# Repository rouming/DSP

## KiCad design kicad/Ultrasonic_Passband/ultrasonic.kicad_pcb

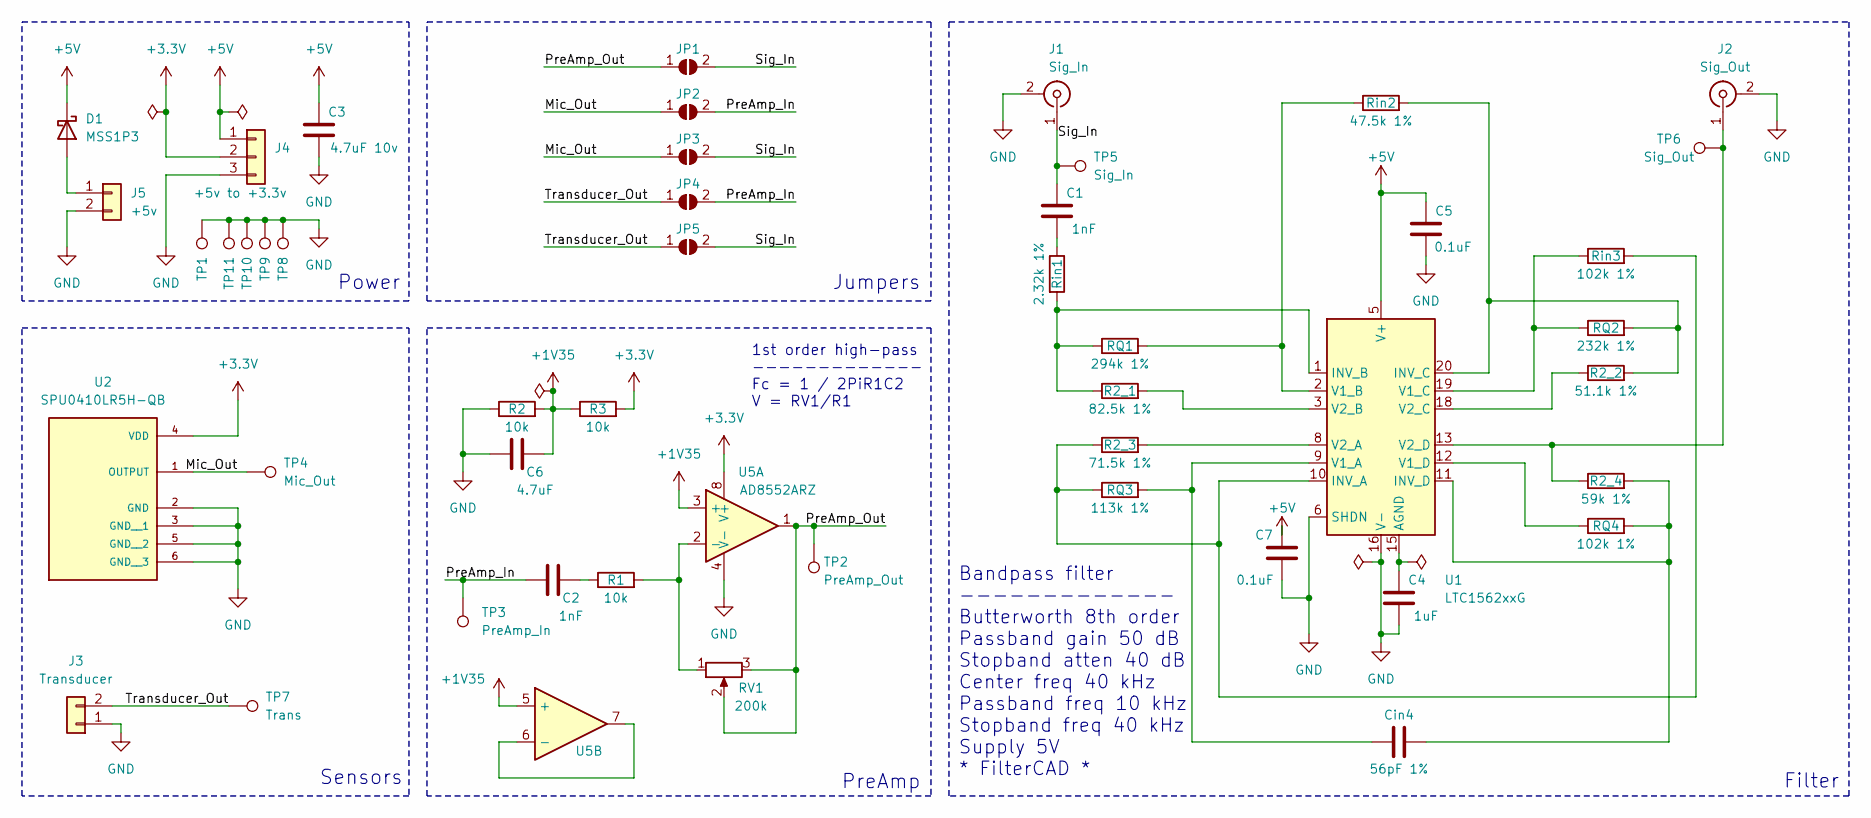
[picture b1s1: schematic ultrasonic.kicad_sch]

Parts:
C1, C2: 1nF; C_0603_1608Metric
C3: 4.7uF 10v; C_0603_1608Metric
C4: 1uF; C_0603_1608Metric
C5, C7: 0.1uF; C_0603_1608Metric
C6: 4.7uF; C_0603_1608Metric
Cin4: 56pF 1%; C_0603_1608Metric
D1: MSS1P3; D_MicroSMP_AK
J1: Sig_In; U.FL_Molex_MCRF_73412-0110_Vertical
J2: Sig_Out; U.FL_Molex_MCRF_73412-0110_Vertical
J3: Transducer; JST_XH_B2B-XH-A_1x02_P2.50mm_Vertical
J4: +5v to +3.3v; PinHeader_1x03_P2.54mm_Vertical
J5: +5v; PinHeader_1x02_P2.54mm_Vertical
JP1: PreAmp > Sig; SolderJumper-2_P1.3mm_Open_RoundedPad1.0x1.5mm
JP2: Mic > PreAmp; SolderJumper-2_P1.3mm_Open_RoundedPad1.0x1.5mm
JP3: Mic > Sig; SolderJumper-2_P1.3mm_Open_RoundedPad1.0x1.5mm
JP4: Trans > PreAmp; SolderJumper-2_P1.3mm_Open_RoundedPad1.0x1.5mm
JP5: Trans > Sig; SolderJumper-2_P1.3mm_Open_RoundedPad1.0x1.5mm
R1, R2, R3: 10k; R_0603_1608Metric
R2_1: 82.5k 1%; R_0603_1608Metric
R2_2: 51.1k 1%; R_0603_1608Metric
R2_3: 71.5k 1%; R_0603_1608Metric
R2_4: 59k 1%; R_0603_1608Metric
RQ1: 294k 1%; R_0603_1608Metric
RQ2: 232k 1%; R_0603_1608Metric
RQ3: 113k 1%; R_0603_1608Metric
RQ4: 102k 1%; R_0603_1608Metric
RV1: 200k; Potentiometer_Bourns_3296W_Vertical
Rin1: 2.32k 1%; R_0603_1608Metric
Rin2: 47.5k 1%; R_0603_1608Metric
Rin3: 102k 1%; R_0603_1608Metric
TP1, TP8, TP9, TP10, TP11: GND; TestPoint_Pad_D2.0mm
TP2: PreAmp_Out; TestPoint_Pad_D2.0mm
TP3: PreAmp_In; TestPoint_Pad_D2.0mm
TP4: Mic_Out; TestPoint_Pad_D2.0mm
TP5: Sig_In; TestPoint_Pad_D2.0mm
TP6: Sig_Out; TestPoint_Pad_D2.0mm
TP7: Trans; TestPoint_Pad_D2.0mm
U1: LTC1562xxG; SSOP-20_5.3x7.2mm_P0.65mm
U2: SPU0410LR5H-QB; XDCR_SPU0410LR5H-QB_aisler; PARTREV H
U5: AD8552ARZ; SOIC-8_3.9x4.9mm_P1.27mm

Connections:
+1V35: C6.1, R2.2, R3.1, U5.3 (+), U5.5 (+)
+3.3V: J4.2, R3.2, U2.4 (VDD), U5.8 (V+)
+5V: C3.1, C5.2, C7.2, D1.1 (K), J4.1, U1.5 (V+)
/Mic_Out: JP2.1 (A), JP3.1 (A), TP4.1, U2.1 (OUTPUT)
/PreAmp_In: C2.2, JP2.2 (B), JP4.2 (B), TP3.1
/PreAmp_Out: JP1.1 (A), RV1.2, RV1.3, TP2.1, U5.1
/Sig_In: C1.2, J1.1 (In), JP1.2 (B), JP3.2 (B), JP5.2 (B), TP5.1
/Transducer_Out: J3.2, JP4.1 (A), JP5.1 (A), TP7.1
GND: C3.2, C4.1, C5.1, C6.2, C7.1, J1.2 (Ext), J2.2 (Ext), J3.1, J4.3, J5.2, R2.1, TP1.1, TP8.1, TP9.1, TP10.1, TP11.1, U1.4 (V-), U1.6 (SHDN), U1.7 (V-), U1.14 (V-), U1.16 (V-), U1.17 (V-), U2.2 (GND), U2.3 (GND__1), U2.5 (GND__2), U2.6 (GND__3), U5.4 (V-)
unnamed: C1.1, Rin1.1
unnamed: C2.1, R1.1
unnamed: D1.2 (A), J5.1
unnamed: J2.1 (In), R2_4.1, TP6.1, U1.13 (V2_D)
unnamed: C4.2, U1.15 (AGND)
unnamed: R2_3.1, RQ3.1, Rin3.2, U1.10 (INV_A)
unnamed: R2_1.1, RQ1.1, Rin1.2, U1.1 (INV_B)
unnamed: R2_2.2, RQ2.2, Rin2.2, U1.20 (INV_C)
unnamed: Cin4.2, R2_4.2, RQ4.2, U1.11 (INV_D)
unnamed: Cin4.1, RQ3.2, U1.9 (V1_A)
unnamed: RQ1.2, Rin2.1, U1.2 (V1_B)
unnamed: RQ2.1, Rin3.1, U1.19 (V1_C)
unnamed: RQ4.1, U1.12 (V1_D)
unnamed: R2_3.2, U1.8 (V2_A)
unnamed: R2_1.2, U1.3 (V2_B)
unnamed: R2_2.1, U1.18 (V2_C)
unnamed: R1.2, RV1.1, U5.2 (-)
unnamed: U5.6 (-), U5.7

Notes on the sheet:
Jumpers
Bandpass filter ------------- Butterworth 8th order Passband gain 50 dB Stopband atten 40 dB Center freq 40 kHz Passband freq 10 kHz Stopband freq 40 kHz Supply 5V * FilterCAD *
Filter
Power
1st order high-pass ------------- Fc = 1 / 2PiR1C2 V = RV1/R1
PreAmp
Sensors

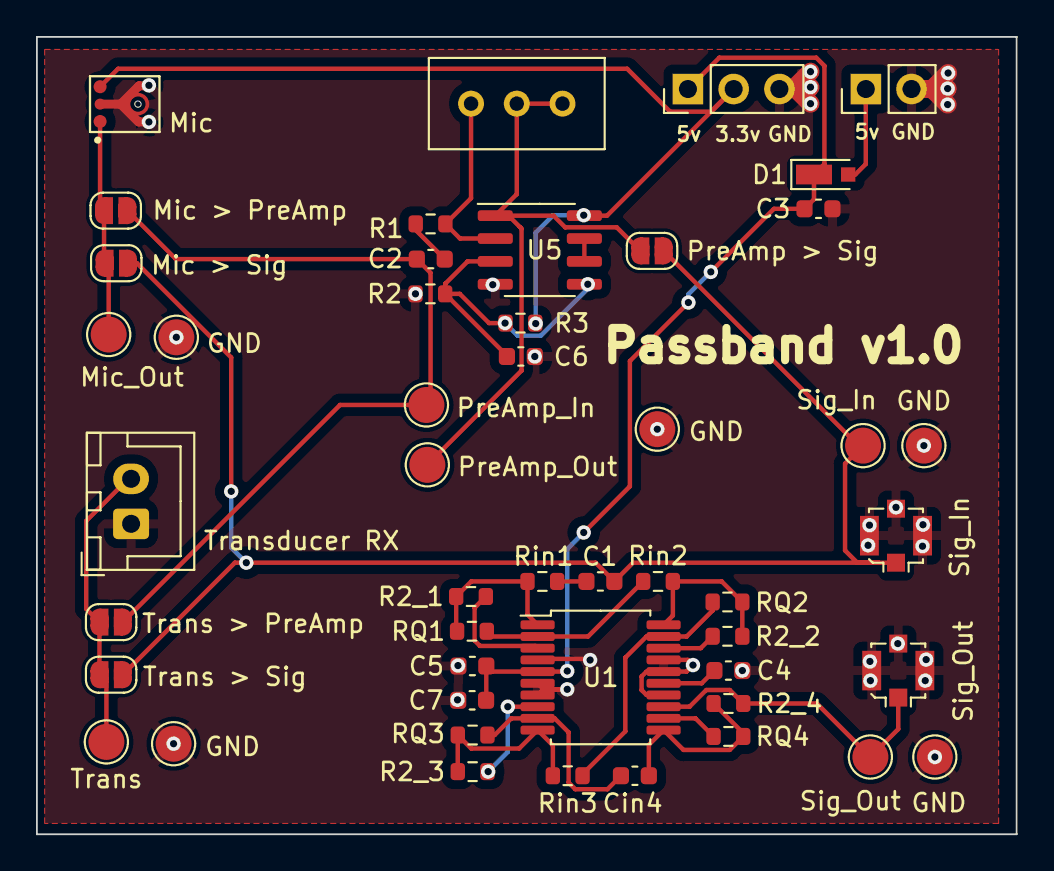
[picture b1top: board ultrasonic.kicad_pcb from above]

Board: 2 copper layers, 54.4 x 44.3 mm, 48 parts (0 on the bottom side), 27 nets.

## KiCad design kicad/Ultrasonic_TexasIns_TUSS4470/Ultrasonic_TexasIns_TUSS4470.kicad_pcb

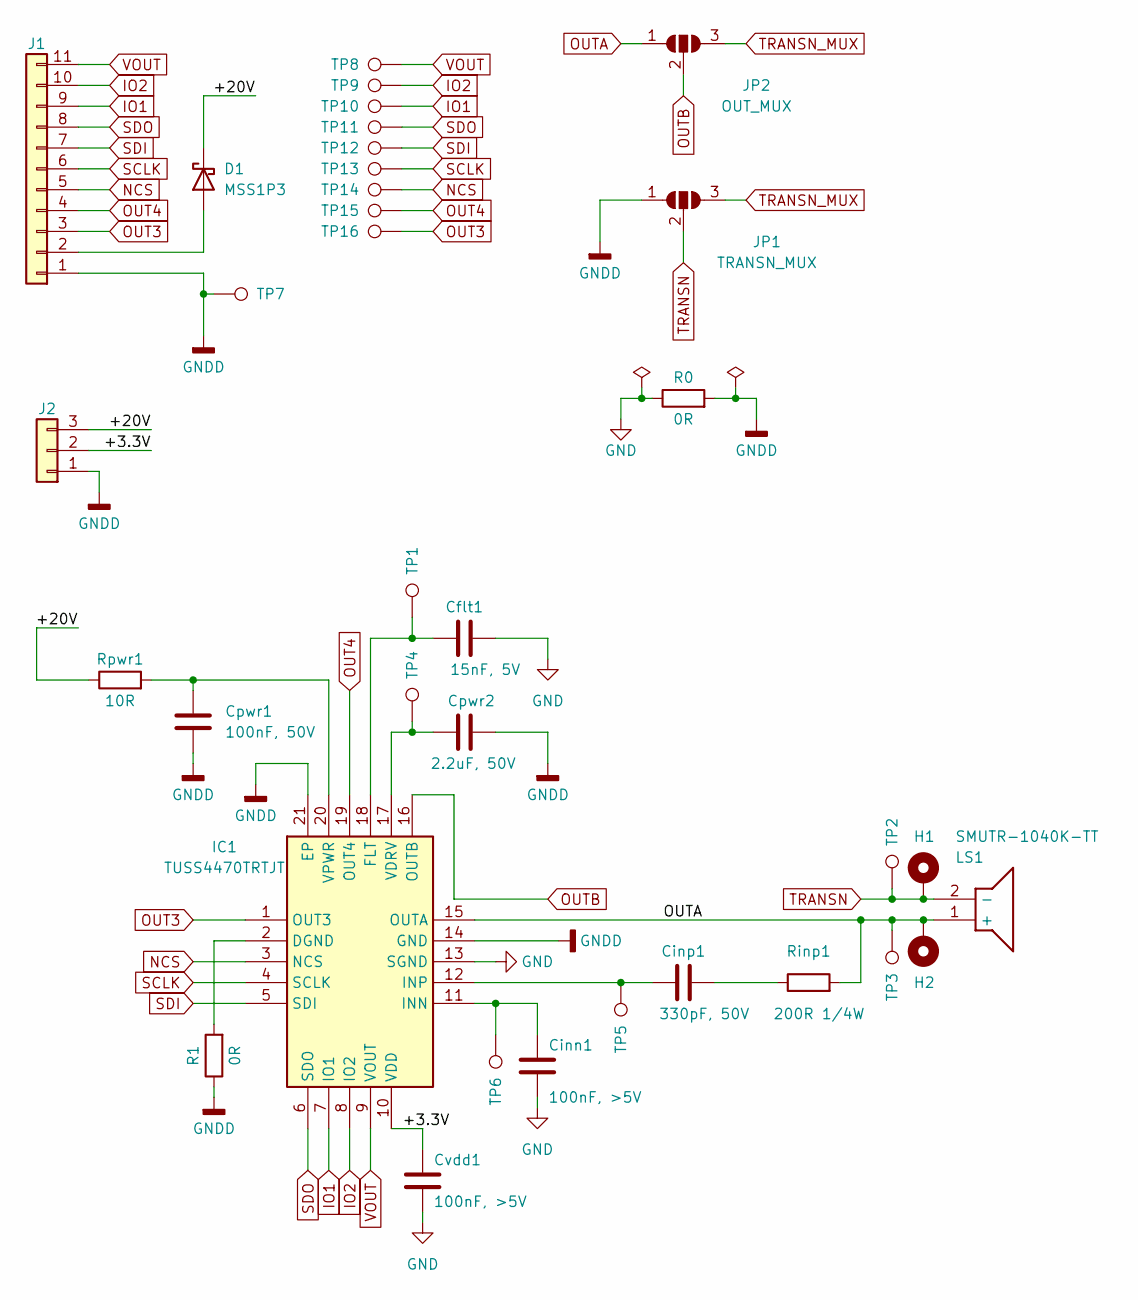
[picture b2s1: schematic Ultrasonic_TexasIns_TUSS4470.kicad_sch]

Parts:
Cflt1: 15nF, 5V; C_0603_1608Metric
Cinn1: 100nF, >5V; C_0603_1608Metric
Cinp1: 330pF, 50V; C_0603_1608Metric
Cpwr1: 100nF, 50V; C_0603_1608Metric
Cpwr2: 2.2uF, 50V; C_0805_2012Metric
Cvdd1: 100nF, >5V; C_0603_1608Metric
D1: MSS1P3; D_MicroSMP_AK
H1, H2: MountingHole_Pad; MountingHole_2.2mm_M2_DIN965_Pad
IC1: TUSS4470TRTJT; QFN50P400X400X80-21N-D; Manufacturer_Part_Number TUSS4470TRTJT; Mouser Part Number 595-TUSS4470TRTJT
J1: PinHeader_1x11_P2.54mm_Vertical
J2: PinHeader_1x03_P2.54mm_Vertical
JP1: TRANSN_MUX; SolderJumper-3_P1.3mm_Open_Pad1.0x1.5mm
JP2: OUT_MUX; SolderJumper-3_P1.3mm_Open_Pad1.0x1.5mm
LS1: SMUTR-1040K-TT; SMUTR1040KTT; Manufacturer_Part_Number SMUTR-1040K-TT
R0, R1: 0R; R_0603_1608Metric
Rinp1: 200R 1/4W; R_0805_2012Metric
Rpwr1: 10R; R_0603_1608Metric
TP1: FLT; TestPoint_Pad_D2.0mm
TP2: TRANSP; TestPoint_Pad_D2.0mm
TP3: TRANSN; TestPoint_Pad_D2.0mm
TP4: VDRV; TestPoint_Pad_D2.0mm
TP5: INP; TestPoint_Pad_D2.0mm
TP6: INN; TestPoint_Pad_D2.0mm
TP7: GND; TestPoint_Pad_D2.0mm
TP8: VOUT; TestPoint_Pad_D1.0mm
TP9: IO2; TestPoint_Pad_D1.0mm
TP10: IO1; TestPoint_Pad_D1.0mm
TP11: SDO; TestPoint_Pad_D1.0mm
TP12: SDI; TestPoint_Pad_D1.0mm
TP13: SCLK; TestPoint_Pad_D1.0mm
TP14: NCS; TestPoint_Pad_D1.0mm
TP15: OUT4; TestPoint_Pad_D1.0mm
TP16: OUT3; TestPoint_Pad_D1.0mm

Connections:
/+3.3V: Cvdd1.1, IC1.10 (VDD), J2.2
/+20V: D1.1 (K), J2.3, Rpwr1.1
GND: Cflt1.2, Cinn1.2, Cvdd1.2, IC1.13 (SGND), R0.1
GNDD: Cpwr1.2, Cpwr2.2, IC1.14 (GND), IC1.21 (EP), J1.1, J2.1, JP1.1 (A), R0.2, R1.1, TP7.1
IO1: IC1.7 (IO1), J1.9, TP10.1
IO2: IC1.8 (IO2), J1.10, TP9.1
NCS: IC1.3 (NCS), J1.5, TP14.1
unnamed: Cinp1.2, Rinp1.1
unnamed: D1.2 (A), J1.2
unnamed: IC1.2 (DGND), R1.2
unnamed: Cflt1.1, IC1.18 (FLT), TP1.1
unnamed: Cinn1.1, IC1.11 (INN), TP6.1
unnamed: Cinp1.1, IC1.12 (INP), TP5.1
unnamed: Cpwr2.1, IC1.17 (VDRV), TP4.1
unnamed: Cpwr1.1, IC1.20 (VPWR), Rpwr1.2
OUT3: IC1.1 (OUT3), J1.3, TP16.1
OUT4: IC1.19 (OUT4), J1.4, TP15.1
OUTA: H2.1, IC1.15 (OUTA), JP2.1 (A), LS1.1 (+), Rinp1.2, TP3.1
OUTB: IC1.16 (OUTB), JP2.2 (C)
SCLK: IC1.4 (SCLK), J1.6, TP13.1
SDI: IC1.5 (SDI), J1.7, TP12.1
SDO: IC1.6 (SDO), J1.8, TP11.1
TRANSN: H1.1, JP1.2 (C), LS1.2 (-), TP2.1
TRANSN_MUX: JP1.3 (B), JP2.3 (B)
VOUT: IC1.9 (VOUT), J1.11, TP8.1

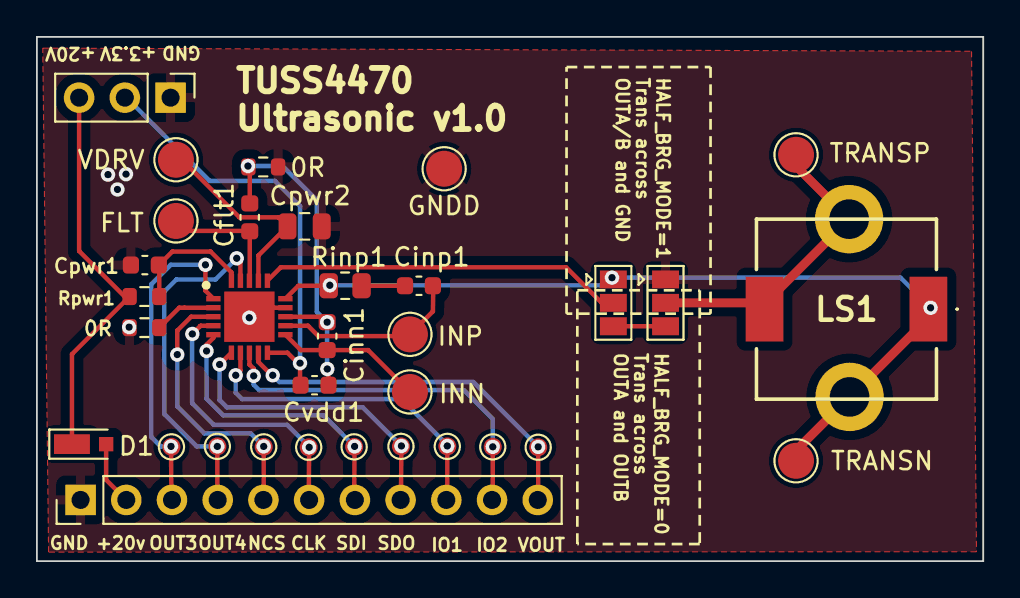
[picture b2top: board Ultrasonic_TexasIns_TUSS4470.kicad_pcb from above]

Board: 2 copper layers, 52.6 x 29.1 mm, 35 parts (0 on the bottom side), 25 nets.

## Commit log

2023-09-14 Initial
2023-09-14 Fixes
2023-09-15 Draw frequencies text
2023-09-22 draw-dfft: implement 2-dim drawing
    Highly inspired by this work:
    https://lubosmato.github.io/drawfft/
2023-09-24 move draw-dfft.py to a separate repo
2024-03-26 Add TUS4470 based on FTDI and python
2024-03-26 tuss4470.py: fix burst
2024-10-05 tuss4470: support custom SET_CLK_PIN command
    Very convenient custom SET_CLK_PIN command for the FT232H-bluepill
    clone, see details here: https://github.com/rouming/FT232H-bluepill
2024-10-05 Add all files + kicad schematics and pcb for ultrasonic and tuss implementation
